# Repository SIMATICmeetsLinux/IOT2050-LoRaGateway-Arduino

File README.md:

# **LoRa-based-IOT-Application**

- [**LoRa-based-IOT-Application**](#lora-based-iot-application)
  - [**Overview**](#overview)
  - [**Hardware**](#hardware)
    - [**LoRaWAN Gateway**](#lorawan-gateway)
      - [**Adapter Shield**](#adapter-shield)
      - [**Concentrator Module iC880A**](#concentrator-module-ic880a)
  - [**Software installation**](#software-installation)
    - [**Preparation of the IOT2050 Platform**](#preparation-of-the-iot2050-platform)
    - [**Enable the SPI-Interface on the IOT2050**](#enable-the-spi-interface-on-the-iot2050)
    - [**Clone LoRa Basics Station from Github**](#clone-lora-basics-station-from-github)
    - [**Adjustments to setup.gmk**](#adjustments-to-setupgmk)
    - [**Building the LoRa Basics Station**](#building-the-lora-basics-station)
    - [**LoRa Basics Station Configuration**](#lora-basics-station-configuration)
    - [**Create files for the authentication mode**](#create-files-for-the-authentication-mode)
    - [**Establish a trust relationship between gateway and server**](#establish-a-trust-relationship-between-gateway-and-server)
    - [**Resetting the iC880A module with the SX1301 baseband chip**](#resetting-the-ic880a-module-with-the-sx1301-baseband-chip)
    - [**Shell script to start Python script automatically**](#shell-script-to-start-python-script-automatically)
    - [**Find out the EUI**](#find-out-the-eui)
    - [**Add the gateway to The Things Stack Community Edition**](#add-the-gateway-to-the-things-stack-community-edition)
    - [**Autostart of the Basic Station on IOT2050**](#autostart-of-the-basic-station-on-iot2050)
    - [**Building an exemplary application**](#building-an-exemplary-application)
      - [**Adding end devices**](#adding-end-devices)
      - [**Visualization of end device data with Node-Red on the IOT2050**](#visualization-of-end-device-data-with-node-red-on-the-iot2050)
  - [**Contribution and Contribution License Agreement**](#contribution-and-contribution-license-agreement))
  - [**Licence and Legal Information**](#licence-and-legal-information)

## **Overview**

This IOT2050 application has the task of collecting data decentralized and transmitting it via radio. The LPWAN technology Long Range (LoRa) is used for this purpose. The IOT2050 serves as a LoRaWAN Gateway. The global, free LoRaWAN (Long Range Wide Area Network) from The Things Network or The Things Stack Community Edition is used as the network server. This manual describes the software and hardware structure of the gateway (the configuration and function of end devices (e.g sensors) is not explained in this manual, because it depends on the individual purpose of the application):

## **Hardware**

The following hardware components are required for the application:

- **SIMATIC IOT2050** as the LoRaWAN-Gateway
- **Adapter Shield** to integrate the iC880A Concentrator to the IOT2050 (self-build) and for the power supply of the concentrator
- **Concentrator Module iC880A** as a LoRaWAN Concentrator module
- **2 dBi Dipole Antenna 863-870MHz with RP SMA** (the selected antenna is based on the frequency range used in Europe from 863 to 870 MHz)
- **U.FL to reverse SMA adapter** as antenna cable

You can also see all individual parts in the [order list](docs/order_list_LoRa_gateway.xlsx).

### **LoRaWAN Gateway**

The Arduino Uno Interface of the SIMATIC IOT2050 is used to integrate the iC880A Concentrator. An adapter shield is required for this purpose, which combines the pin assignments. The concentrator is supplied with 5V.

#### **Adapter Shield**

The adapter shield used in this application was self-built. The required components can be taken from the [order list](docs/order_list_LoRa_gateway.xlsx). Further information about the structure can be found in [the project file (.pro)](docs/adapter%20shield/iC880A_shield_v1.2.pro), [the schematic file (.sch)](docs/adapter%20shield/iC880A_shield_v1.2.sch) and [the layout file (.kicad_pcb)](docs/adapter%20shield/iC880A_shield_v1.2.kicad_pcb).

#### **Concentrator Module iC880A**

The LoRaWAN Concentrator iC880A is a multi-channel high performance transmitter/receiver module designed to receive several LoRa packets simultaneously using different spreading factors on multiple channels. The concentrator module iC880A can be integrated into a gateway as a complete RF front end of this gateway.

The following figure shows the complete hardware structure of the LoRaWAN gateway. To connect the antenna (2 dBi Dipole Antenna 863-870MHz with RP SMA) to the iC880A module, a U.FL to reverse SMA adapter is used. The concentrator is plugged into the Arduino Uno interface of the IOT2050 together with the adapter shield.

## **Software installation**

The following software is used for this manual:

- **LoRa Basics™ Station** for an implementation of a LoRa® packet forwarder. A LoRa packet forwarder is a program running on the host of a LoRa-based gateway. It forwards RF packets received by the concentrator (uplinks) to a LoRaWAN® Network Server (LNS) through a secured IP link ([more information](https://doc.sm.tc/station/) - [Github Link](https://github.com/lorabasics/basicstation.git))
- **The LoRaWAN Network Server from The Things Industry** is at the core of every LoRaWAN Network that enables connectivity, management, and monitoring of devices, gateways and end-user applications. Its main objectives are to ensure the security, scalability and reliability of data routing throughout the network. (registration required! - [more information](https://www.thethingsindustries.com/news/what-lorawan-network-server/))
- **IOT2050 Example Image as of V1.1.1** as Linux operating system for the IOT2050. Can be downloaded [here](https://support.industry.siemens.com/cs/de/en/view/109780231)

### **Preparation of the IOT2050 Platform**
For the first commissioning of the IOT2050 please refer to the [Setting Up](https://github.com/SIMATICmeetsLinux/IOT2050-SmartFarming-Application/blob/main/docs/SIMATIC_IOT2050_setting_up.md). 
You can get further help in [the SIMATIC IOT2050 forum](https://support.industry.siemens.com/tf/ww/en/threads/309).

After working through the Setting Up, an update must be performed for the system and *git* must be installed. The following commands are executed for this:

    sudo apt-get update
    sudo apt-get install git

### **Enable the SPI-Interface on the IOT2050**

Establish a shh connection via putty and use the following commands:

    iot2050setup
    Use the arrow keys: "Peripherals" -> "Configure Arduino I/O" -> "Enable SPI on IO10-IO13" -> "Enable"
    Use ESC to exit the iot2050setup

### **Clone LoRa Basics Station from Github**

To clone the latest version of LoRa Basics™ Station from Github use the following commands:

    cd /home
    git clone https://github.com/lorabasics/basicstation.git

### **Adjustments to setup.gmk**

Now the `setup.gmk` file, which is part of the clone, must be adapted for the IOT2050 to store the correct directories for the toolchain. To do this, open the file in an editor using the following commands:

    cd /home/basicstation/
    nano setup.gmk

With the key combination `CTRL+C` a line specification can be shown in the nano-editor:

Lines 55 - 66 must be commented out with `#` and lines 68 - 72 must be changed to the following:

    CC=/usr/bin/gcc
    LD=/usr/bin/ld
    AR=/usr/bin/ar
    OD=/usr/bin/objdump
    OC=/usr/bin/objcopy

In addition, line 76 must be edited as follows:

    export LD_LIBRARY_PATH=/usr/local/lib

Save and close the file with the following commands:

    CTRL+X -> to exit editing
    Y -> to save the changes
    Enter -> to confirm the filename

### **Building the LoRa Basics Station**

To build the package forwarder station use the following command in the directory `/home/basicstation/`:

    make platform=rpi variant=std

After the Basic Station has been compiled, a new folder called `build-rpi-std` with four subfolders has appeared. You can find the compiled binary `station` in the subfolder `bin`.

**Unless otherwise specified, the following commands and actions are always executed in this directory (`/home/basicstation/build-rpi-std/bin/`).**

### **LoRa Basics Station Configuration**

Some configurations are needed for the Basic Station, which are specified in the file `station.conf`. Copy the ready-made file [station.conf](src/station.conf) into the directory (Tip: The tool WINSCP can be used to transfer the files).

### **Create files for the authentication mode**

The LoRa Basics™ Station needs to be provided with the LoRaWAN® Network Server (LNS) to connect to. For this example The Things Stack Community Edition server with port 8887 is used. This is specified in the file `tc.uri`. Copy the ready-made file [tc.uri](src/tc.uri) into the directory.

### **Establish a trust relationship between gateway and server**

This requires a root certificate. The following command can be used to get a certificate and create the file `tc.trust` directly:

    curl https://letsencrypt.org/certs/isrgrootx1.pem.txt -o tc.trust

You can also use another root certificate, which needs to be inserted into the `tc.trust` file without the characters `<>`:

    -----BEGIN CERTIFICATE-----
    <insert root certificate here>
    -----END CERTIFICATE-----

### **Resetting the iC880A module with the SX1301 baseband chip**

The iC880A module with the SX1301 baseband chip must be reset every time it is switched on. However, this reset is not performed by the HAL of the chip. Therefor a Python script is written to carry that out externally. Copy the Python script [iC880A_Reset.py](src/iC880A_Reset.py) into the directory. Afterwards the Digital I/O PIN 4 must be set as output, because this is used as reset pin:

    iot2050setup
    Use the arrow keys: "Peripherals" -> "Configure Arduino I/O" -> "Enable GPIO" -> Set PIN 4 as output
    Use ESC to exit the iot2050setup

### **Shell script to start Python script automatically**

The next step is to add a shell script that executes the Python script. This script will later be executed with the start of the `station` binary. Copy the ready-made file [reset_gw.sh](src/reset_gw.sh) into the directory. In this shell script, the previously created Python script for the hardware reset of the concentrator is called. The script needs now to be provided with executable rights with the following command:

    chmod 755 reset_gw.sh

### **Find out the EUI**

To get the EUI of the gateway for registration at the server, the program `station` needs to be started once (execution is not fully functional yet):

    ./station

The EUI of the gateway is composed of the MAC address of the IOT2050 and is displayed in the console output after the station has been started:

The application can be stopped with the key combination `CTRL+C`.

### **Add the gateway to The Things Stack Community Edition**

Finally, to authorize the gateway with [The Things Stack Community Edition](https://eu1.cloud.thethings.network/console/gateways), an API key must be stored in a file called `tc.key`. To do this, the gateway must be registered at [The Things Stack Community Edition](https://eu1.cloud.thethings.network/console/gateways). This is explained in the following steps: After logging into the webpage, the region is selected. After that a new gateway can be added. For this, a unique gateway ID must be entered, as well as the gateway EUI from the previous figure. In addition, the frequency plan for the region is selected. Furthermore, it can be selected whether the status of the gateway is publicly visible. All required configurations are shown in the following figure:

After registering the new gateway, an API Key must be generated for authorization. Before the key is generated, it is assigned a name. In addition, it is given individual rights for linking as a gateway with a gateway server for data exchange. **After the creation of the API key it must be copied and stored urgently, because it is encrypted afterwards and therefore no longer visible.**

Use the following commands to build the `tc.key` file and use the previously copied API key instead of `xxx`:

    export LNS_KEY="xxx"
    echo "Authorization: Bearer $LNS_KEY" | perl -p -e 's/\r\n|\n|\r/\r\n/g' > tc.key

This completes the installation and configuration of the Basic Station. Now the the station can be started manually with the command:

    ./station

If the installation and authentication are successful, the station starts and the gateway is displayed as `connected` in the console of The Things Stack Community Edition:

You can receive further information on the [The Things Stack Website - Adding Gateways](https://www.thethingsindustries.com/docs/gateways/adding-gateways/).

### **Autostart of the Basic Station on IOT2050**

Copy the ready-made shell script [start.sh](src/start.sh), which call the `station` binary, into the directory. The script must then be provided with executable rights:

    chmod 755 start.sh

Copy the ready-made systemd service file [iot-2050-lora-gateway.service](src/iot2050-lora-gateway.service) into the directory `/etc/systemd/system`. To change to that directory use the following command:

    cd /etc/systemd/system

The service file can now be started manually and tested with the following command:

    sudo systemctl start iot2050-lora-gateway.service

After successful start of the service and the station, it can be terminated with the following command:

    sudo systemctl stop iot2050-lora-gateway.service

To enable the autostart of the service use the command

    sudo systemctl enable iot2050-lora-gateway.service

After the next reboot, the gateway will be started with every boot.

### **Building an exemplary application**

#### **Adding end devices**

The gateway is now ready for use. End devices can now be added to the application via The Things Stack Community Edition, which then transmit data via the gateway to the server. [Here you can find some possible end devices.](https://www.thethingsnetwork.org/marketplace/products/devices) How to add end devices on the server is described [here](https://www.thethingsindustries.com/docs/devices/adding-devices/)

#### **Visualization of end device data with Node-Red on the IOT2050**

Node-Red is used to visualize the collected data. The web editor is accessible via the IP address of the IOT2050 and port 1880. Node-red is in autostart by default on the Example Image. To access it, open a browser on your PC connected to the IOT2050 and open the URL `http://<IP of the IOT2050>:1880/`.

Now the [flows.json](src/flows.json) file can be imported into Node-Red:

    Menu -> Import -> Select file for Upload

The nodes must be adjusted as follows:

**MQTT:** Insert the server address and the port of The Things Stack in the connection tab.  To subscribe all messages set *Topic* to `#`.

Enter your *Username* and the *MQTT-API-Key* as the *Password*. You can generate this API-Key in the integrations-settings of your application:

**Parse Node:** In the function *Parse Node* the different `device_id` must be adjusted (depending on the application):

**Description of the flow:** To process the incoming messages, a Javascript object is created first. Then the uplinks are parsed in the function *Parse Node* to extract the individual messages of each end device. In addition, the node is extended to three outputs. Thus, each message is assigned to an output and stands for an end device. Using the dashboard library and the gauge node, these can then be individually built into a dashboard.

The pre-build flow shows an example of the combination of three end devices in the parse node. The ID's must be adjusted depending on the application and the setting in The Things Network.

**Dashboard:** To display the data, the Dashboard palette can now be installed and individually configured:

    Menu -> Manage Palette -> Install Tab -> Search and install the given libraries

- node-red-dashboard

**Completion:** To download the flow to the IOT2050 click on the button `Deploy`

To open the dashboard of node-red open the URL `http://<IP of the IOT2050>:1880/ui`

## **Contribution and Contribution License Agreement**

Thank you for your interest in contributing. Anybody is free to report bugs, unclear documentation, and other problems regarding this repository in the Issues section.
Additionally everybody is free to propose any changes to this repository using Pull Requests.

If you haven't previously signed the [Siemens Contributor License Agreement](https://cla-assistant.io/industrial-edge/) (CLA), the system will automatically prompt you to do so when you submit your Pull Request. This can be conveniently done through the CLA Assistant's online platform. Once the CLA is signed, your Pull Request will automatically be cleared and made ready for merging if all other test stages succeed.

## **Licence and Legal Information**

Please read the [Legal information](LICENSE.md).

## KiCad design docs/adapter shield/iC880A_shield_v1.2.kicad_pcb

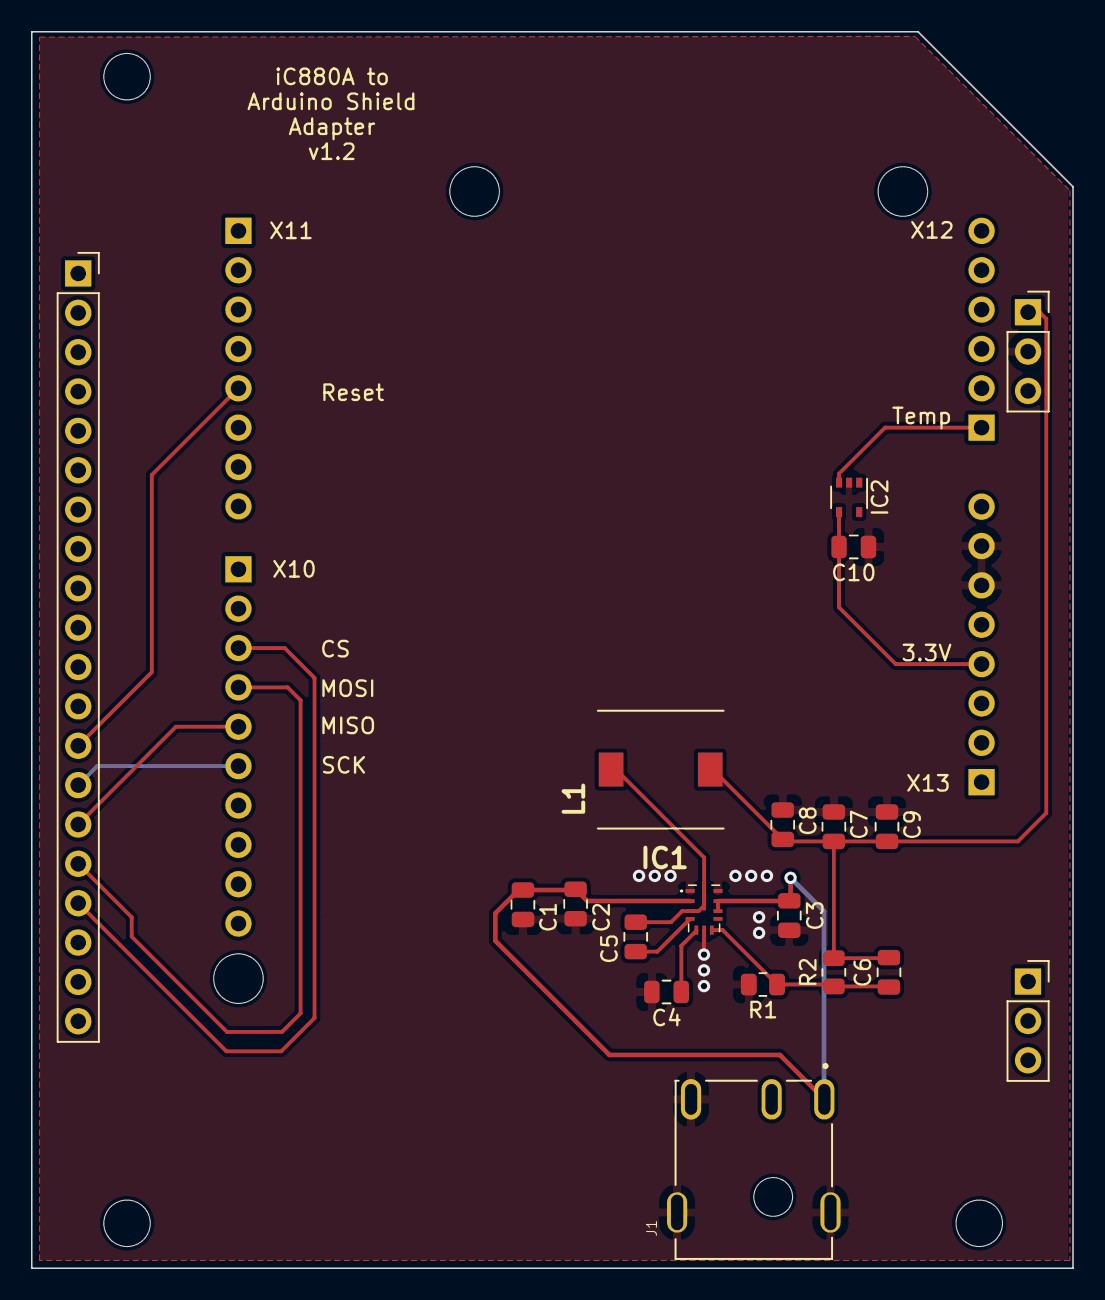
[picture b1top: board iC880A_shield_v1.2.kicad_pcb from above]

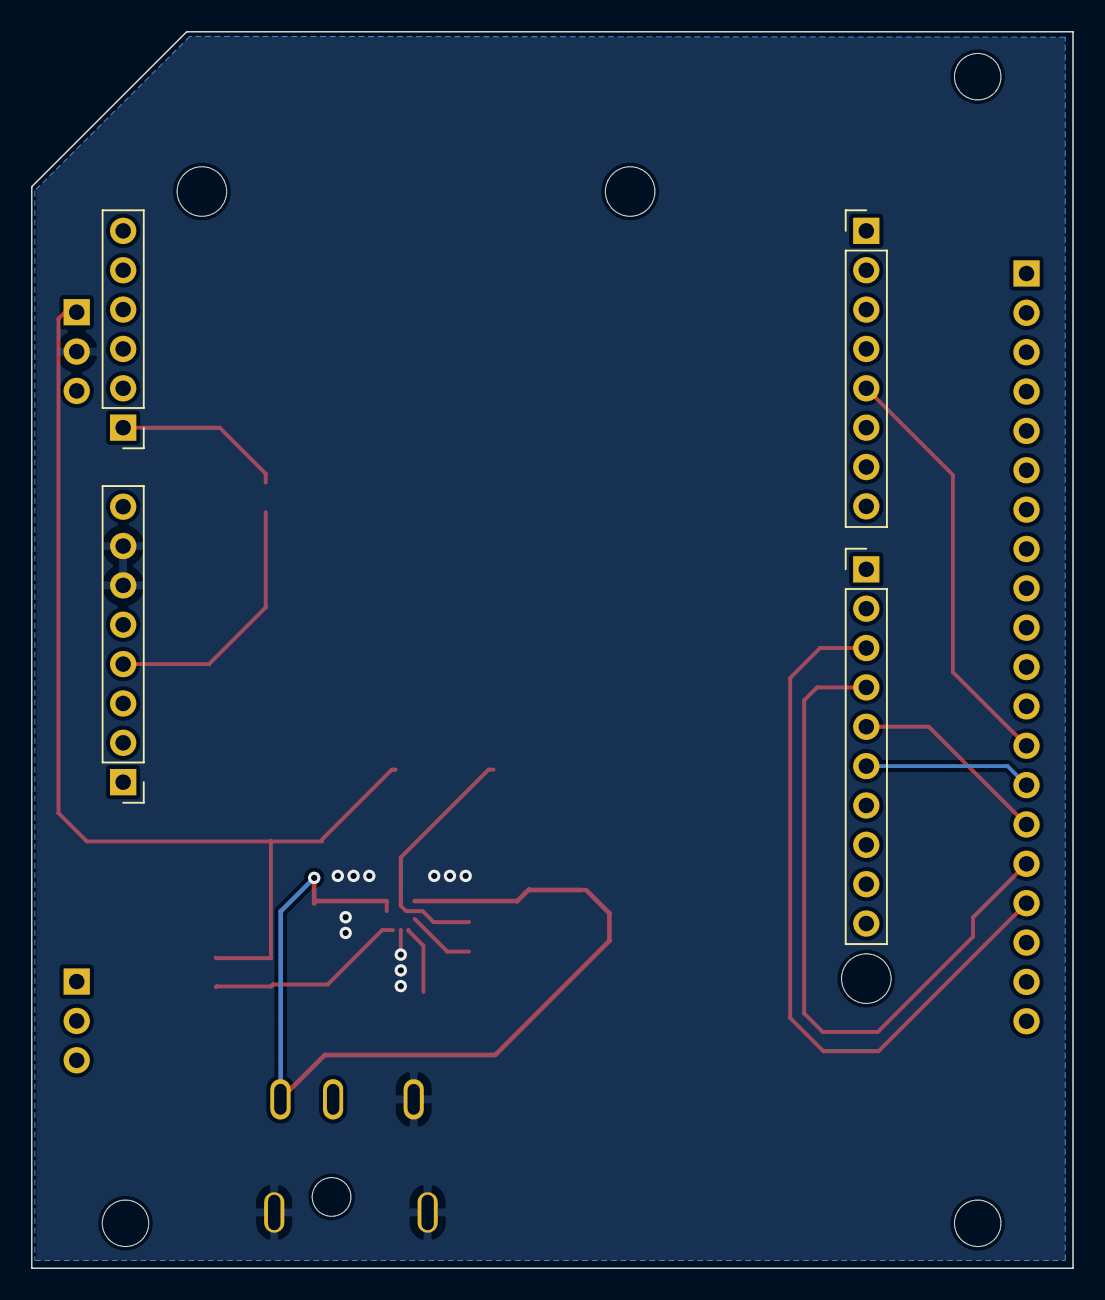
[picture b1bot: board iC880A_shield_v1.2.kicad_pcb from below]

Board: 2 copper layers, 67.2 x 79.8 mm, 29 parts (4 on the bottom side), 14 nets.

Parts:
C1: 4.7uF; C_0805_2012Metric
C2, C3: 220nF; C_0805_2012Metric
C4: 1uF; C_0805_2012Metric
C5, C10: 100nF; C_0805_2012Metric
C6: 20pF; C_0805_2012Metric
C7, C8, C9: 22uF; C_0805_2012Metric
H1, H2, H3: MountingHole; MountingHole_3mm
H4, H5, H6: MountingHole; MountingHole_3.2mm_M3
IC1: LMR36015ARNXT; LMR36015FSCQRNXTQ1
IC2: MCP9700AT-ELT; SOT-353_SC-70-5
J1: PJ-079AH; CUI_PJ-079AH
J2, J3: Conn_01x03_Female; PinSocket_1x03_P2.54mm_Vertical
J4: Conn_01x20_Female; PinSocket_1x20_P2.54mm_Vertical
J5: Conn_01x10_Male; PinHeader_1x10_P2.54mm_Vertical
J6, J8: Conn_01x08_Male; PinHeader_1x08_P2.54mm_Vertical
J7: Conn_01x06_Male; PinHeader_1x06_P2.54mm_Vertical
L1: 10uH; WE-PD_7332_7345_PLASTIC_BASE54
R1: 24.9k; R_0805_2012Metric
R2: 100k; R_0805_2012Metric

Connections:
/5V: C6.2, C7.1, C8.1, C9.1, J3.1, L1.2, R2.2
/24V: C1.1, C2.1, C3.1, IC1.2, IC1.9, IC1.10, J1.1
/CLK: J4.14, J5.6
/CS: J4.17, J5.3
/MISO: J4.15, J5.5
/MOSI: J4.16, J5.4
/RESET: J4.13, J8.5
/TEMP: IC2.3, J7.1
/Vcc: C10.2, IC2.4, J6.4
GND: C1.2, C2.2, C3.2, C4.2, C7.2, C8.2, C9.2, C10.1, IC1.1, IC1.6, IC1.11, IC2.2, J1.2, J1.S1, J1.S2, J3.2, J6.6, J6.7, R1.2
unnamed: C4.1, IC1.5
unnamed: C5.1, IC1.3, IC1.12, L1.1
unnamed: C5.2, IC1.4
unnamed: C6.1, IC1.7, R1.1, R2.1

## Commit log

2021-08-09 Create branch
    Upload prepared files
2021-10-05 Remove "building image"
    V1.1.1 is now available as download
2022-03-14 Upload CLA 1.1 PDF
2023-10-13 Update README.md
    Change CLA process

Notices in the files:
README.md:
Thank you for your interest in contributing. Anybody is free to report bugs, unclear documentation, and other problems regarding this repository in the Issues section.
Additionally everybody is free to propose any changes to this repository using Pull Requests.
If you haven't previously signed the [Siemens Contributor License Agreement](https://cla-assistant.io/industrial-edge/) (CLA), the system will automatically prompt you to do so when you submit your Pull Request. This can be conveniently done through the CLA Assistant's online platform. Once the CLA is signed, your Pull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
